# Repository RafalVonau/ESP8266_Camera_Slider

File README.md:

# Camera slider on ESP8266

## Info

This repository contains the software for my ESP8266 based Camera slider.

Features:
- No collision-detection!!
- WWW page interface ( http://slider.local ),
- Simple commands over TCP (port 2500),
   from linux:
      netcat slider.local 2500
- Simple commands over HTTP POST ( http://slider.local/post ),
- Set mottor current and microsteps per step by a command (software),
- Optional endstop switch for homing.

# Mechanical parts needed:
* 3D printed pars,
* 1 x T8 Trapezoidal Lead Screw L=500mm,
* 1 x T8 Brass Nut,
* 2 x KP08 Bore Ball Bearing Pillow Block Mounted Support 8mm,
* 2 x 8mm Inner Dia L=34.5mm SCS8UU Linear Bearing,
* 2 x Aluminum 8mm Innner Dia 42x32x11mm SK8 Linear Rod Rail Support Guide Shaft Bearing
* 2 x Linear Shaft Optical Axis 8mm L=500mm,
* 4 x SK8 Linear Rod Rail Shaft,
* 1 x T8 Nut Conversion Seat,
* screws

# Electrical parts needed:
* ESP8266 (bare ESP8266 module or D1 mini),
* DC/DC converter 12V to 3.3V,
* 1 x TMC2208,
* 1 x Stepper motor Nema 17,
* wires,
* connectors,
* [1 x Limit Switch Endstop for Creality CR-10 10S Ender 3] - OPTIONAL

# D1 mini CONNECTIONS
* STEP      - GPIO14 (D5)
* DIR1      - GPIO13 (D7)
* MOTTOR EN - GPIO2  (D4)
* RX        - TMC2208 single wire UART (1kohm from RX to TX)
* TX        - TMC2208 single wire UART (1kohm from RX to TX)
* ENDSTOP   - GPIO4  (D2)  - OPTIONAL
# Wiring

# Software architecture

The ESP8266 generates STEP and DIR signals to the TMC2208 chip for motor movement. The UART connection allows you to program the TMC2208 chip registers so you can easily change the current and the number of micro steps per step without having to turn a potentiometer or change jumpers. 

STEP signal is generated using Timer1 (for performance reasons the interrupt control was taken from this timer and it was set to AUTORELOAD mode) and because Timer1 is used in servo/pwm(analogWrite)/tone/waveform functions these functions can't be used in this code. 

Commands are received on the fly from TCP channels (port 2500) and the WWW page (POST) and then passed to the command queue. The movement commands are passed to a separate queue so that sequences of movements can be queued. When the move is completed, the next command from the move queue is taken, and so on.

# Building

Uncomment and modify Wifi client settings in secrets.h file:
* #define WIFI_SSID                "Slider"
* #define WIFI_PASS                "SliderPass"

The project uses platformio build environment. 
[PlatformIO](https://platformio.org/) - Professional collaborative platform for embedded development.

* install PlatformIO
* enter project directory
* connect ESP8266 to PC computer over USB to serial cable.
* type in terminal:
  platformio run -t upload

You can also use IDE to build this project on Linux/Windows/Mac. My fvorite ones:
* [Code](https://code.visualstudio.com/) 
* [Atom](https://atom.io/)

# Commands
EM  - enable mottors,

Movement in revolutions:\
M   - absolute move in motor revolutions (M,duration [ms],start_rev,target_rev),\
MR  - relative move in motor revolutions (MR,duration [ms],delta rev),\
MH  - move to home (endstop switch is required),

Movement in microsteps:\
GT  - absolute move in microsteps (GT,duration [ms],start_microstep,target_microstep)\
GTR - relative move in microsteps (GTR,duration [ms],delta microsteps)\
GTH - move to home (endstop switch is required),\
UM  - unconditional relative move in microsteps WARNING: do not check limits. (UM,duration [ms],delta microsteps)

STP - STOP move,

Parameters set:\
G90 - Set this possition as zero point,\
C   - set motor current in [mA],\
S   - set microsteps per step,

STATUS:\
XX  - print status,

Examples:

set mottor curent to 400mA:

C,400

Set 32 misrosteps per step:

S,32

Move from revolution 1 to 45 in 30000 miliseconds:

M,30000,1,45

Move 1 revolution in backward direction in 2 seconds:

MR,2000,1

Stop move:

STP

Enjoy :-)

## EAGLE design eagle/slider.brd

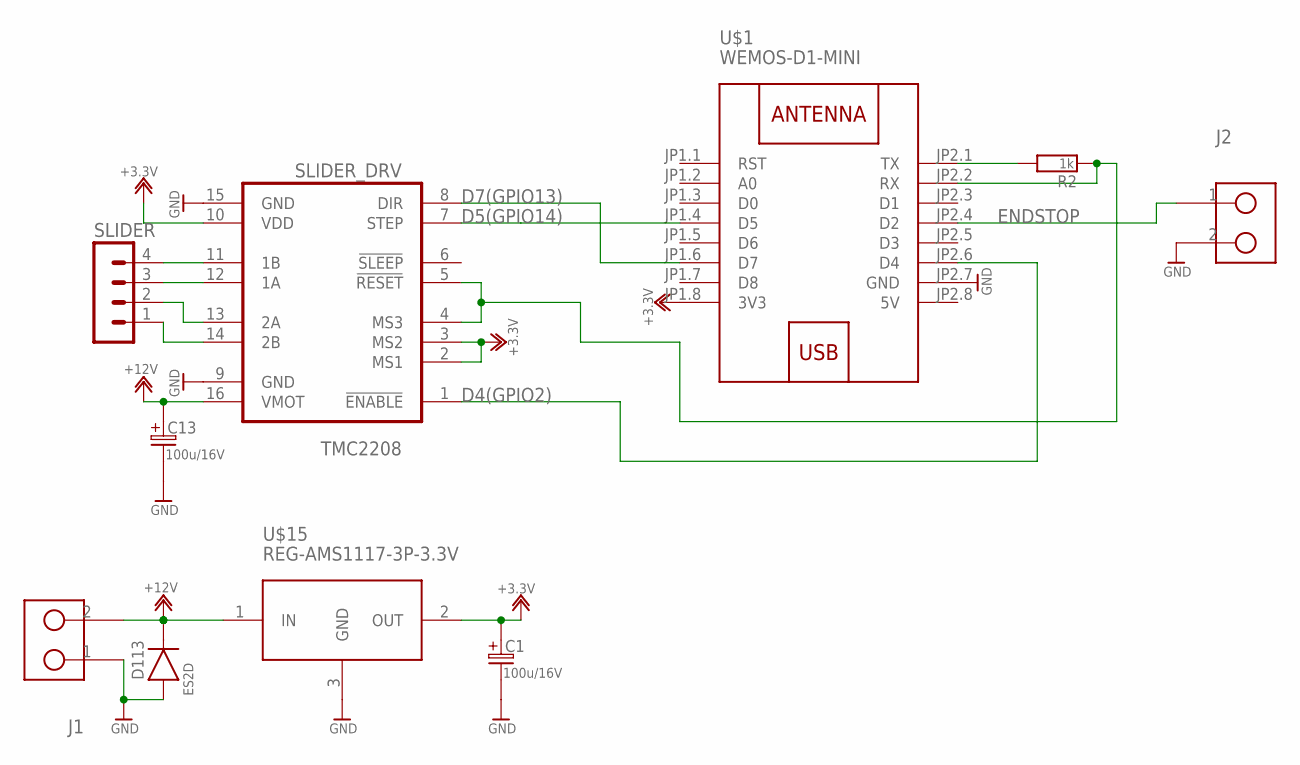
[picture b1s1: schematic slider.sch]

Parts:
C1, C13: 100u/16V; ES-3,5/8
D113: ES2D; SMB
J1, J2: GMKDS-2; GMKDS1,5
R2: 1k; 0805
SLIDER: MA04-1
SLIDER_DRV: TMC2208; POLOLULU2128
U$1: WEMOS-D1-MINI
U$15: REG-AMS1117-3P-3.3V; REG-AMS1117-3P

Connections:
5V: U$1.JP2.8 (5V)
+3.3V: C1.1, SLIDER_DRV.2 (MS1), SLIDER_DRV.3 (MS2), SLIDER_DRV.10 (VDD), U$1.JP1.8 (3V3), U$15.2 (OUT)
+12V: C13.1, D113.2 (K), J1.2, SLIDER_DRV.16 (VMOT), U$15.1 (IN)
D4(GPIO2): SLIDER_DRV.1 (!ENABLE), U$1.JP2.6 (D4)
D5(GPIO14): SLIDER_DRV.7 (STEP), U$1.JP1.4 (D5)
D7(GPIO13): SLIDER_DRV.8 (DIR), U$1.JP1.6 (D7)
ENDSTOP: J2.1, U$1.JP2.4 (D2)
GND: C1.2, C13.2, D113.1 (A), J1.1, J2.2, SLIDER_DRV.9 (GND), SLIDER_DRV.15 (GND), U$1.JP2.7 (GND), U$15.3 (GND)
unnamed: R2.2, U$1.JP2.1 (TX)
unnamed: R2.1, SLIDER_DRV.4 (MS3), SLIDER_DRV.5 (!RESET), U$1.JP2.2 (RX)
unnamed: SLIDER.4, SLIDER_DRV.11 (1B)
unnamed: SLIDER.3, SLIDER_DRV.12 (1A)
unnamed: SLIDER.2, SLIDER_DRV.13 (2A)
unnamed: SLIDER.1, SLIDER_DRV.14 (2B)

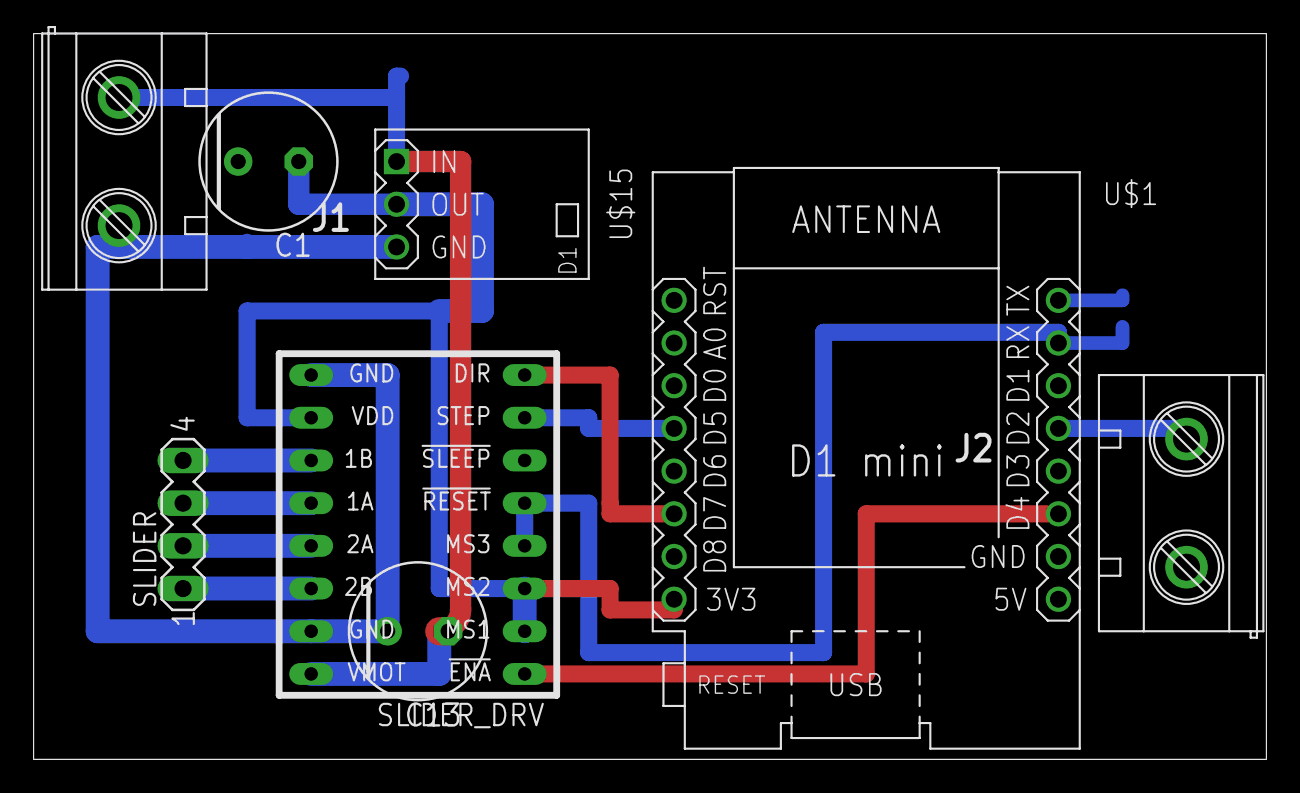
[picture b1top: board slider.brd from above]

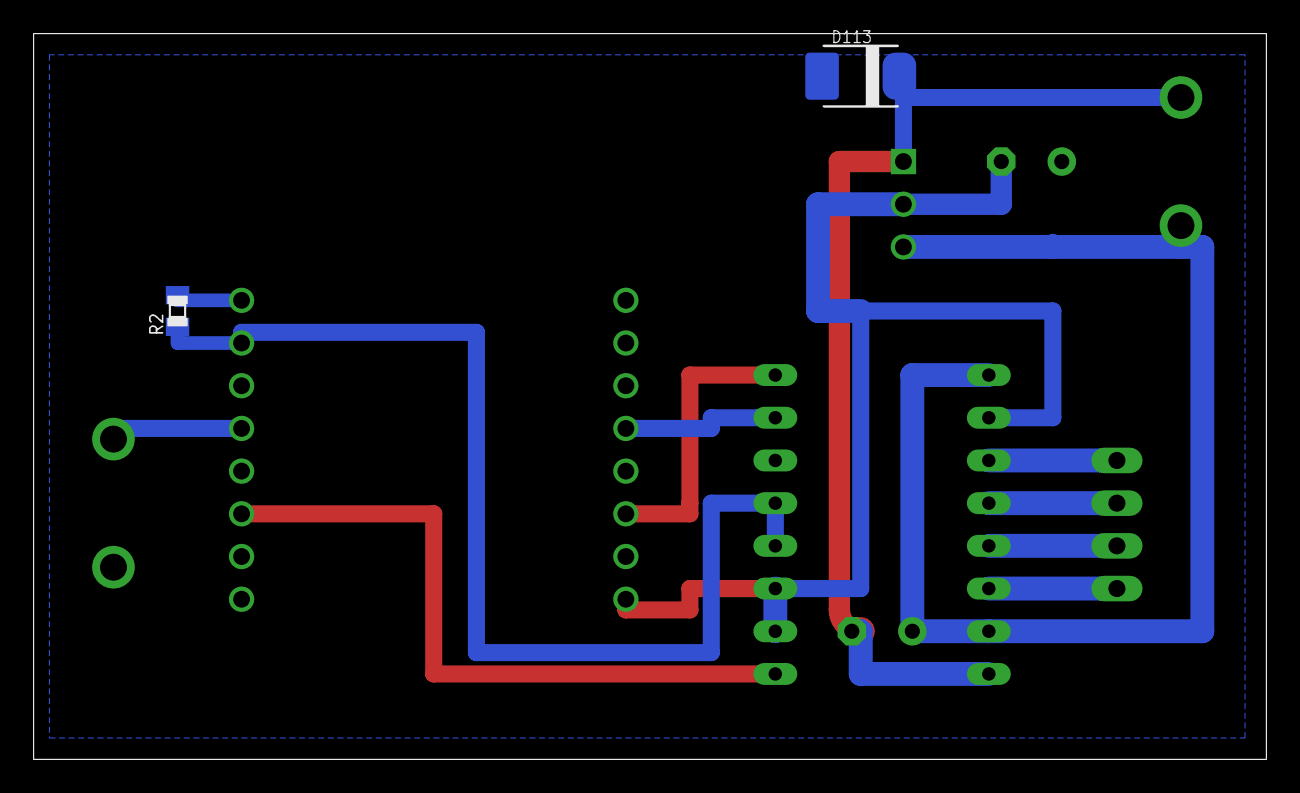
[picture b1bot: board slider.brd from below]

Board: 2 copper layers, 73.3 x 43.2 mm, 10 parts (2 on the bottom side), 13 nets.

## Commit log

2021-11-09 Initial import
2021-11-09 STL and JPEG files
2021-11-10 Optional endstop for homming
2021-11-10 Schematic fixups
2021-11-10 gcode fixups
2021-11-10 fixups
2021-11-10 endstop stl file
2021-11-19 Ramp support

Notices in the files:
parts and their libraries:
diy-modules: Released under the Creative Commons Attribution 4.0 International License: http://creativecommons.org/licenses/by/4.0
